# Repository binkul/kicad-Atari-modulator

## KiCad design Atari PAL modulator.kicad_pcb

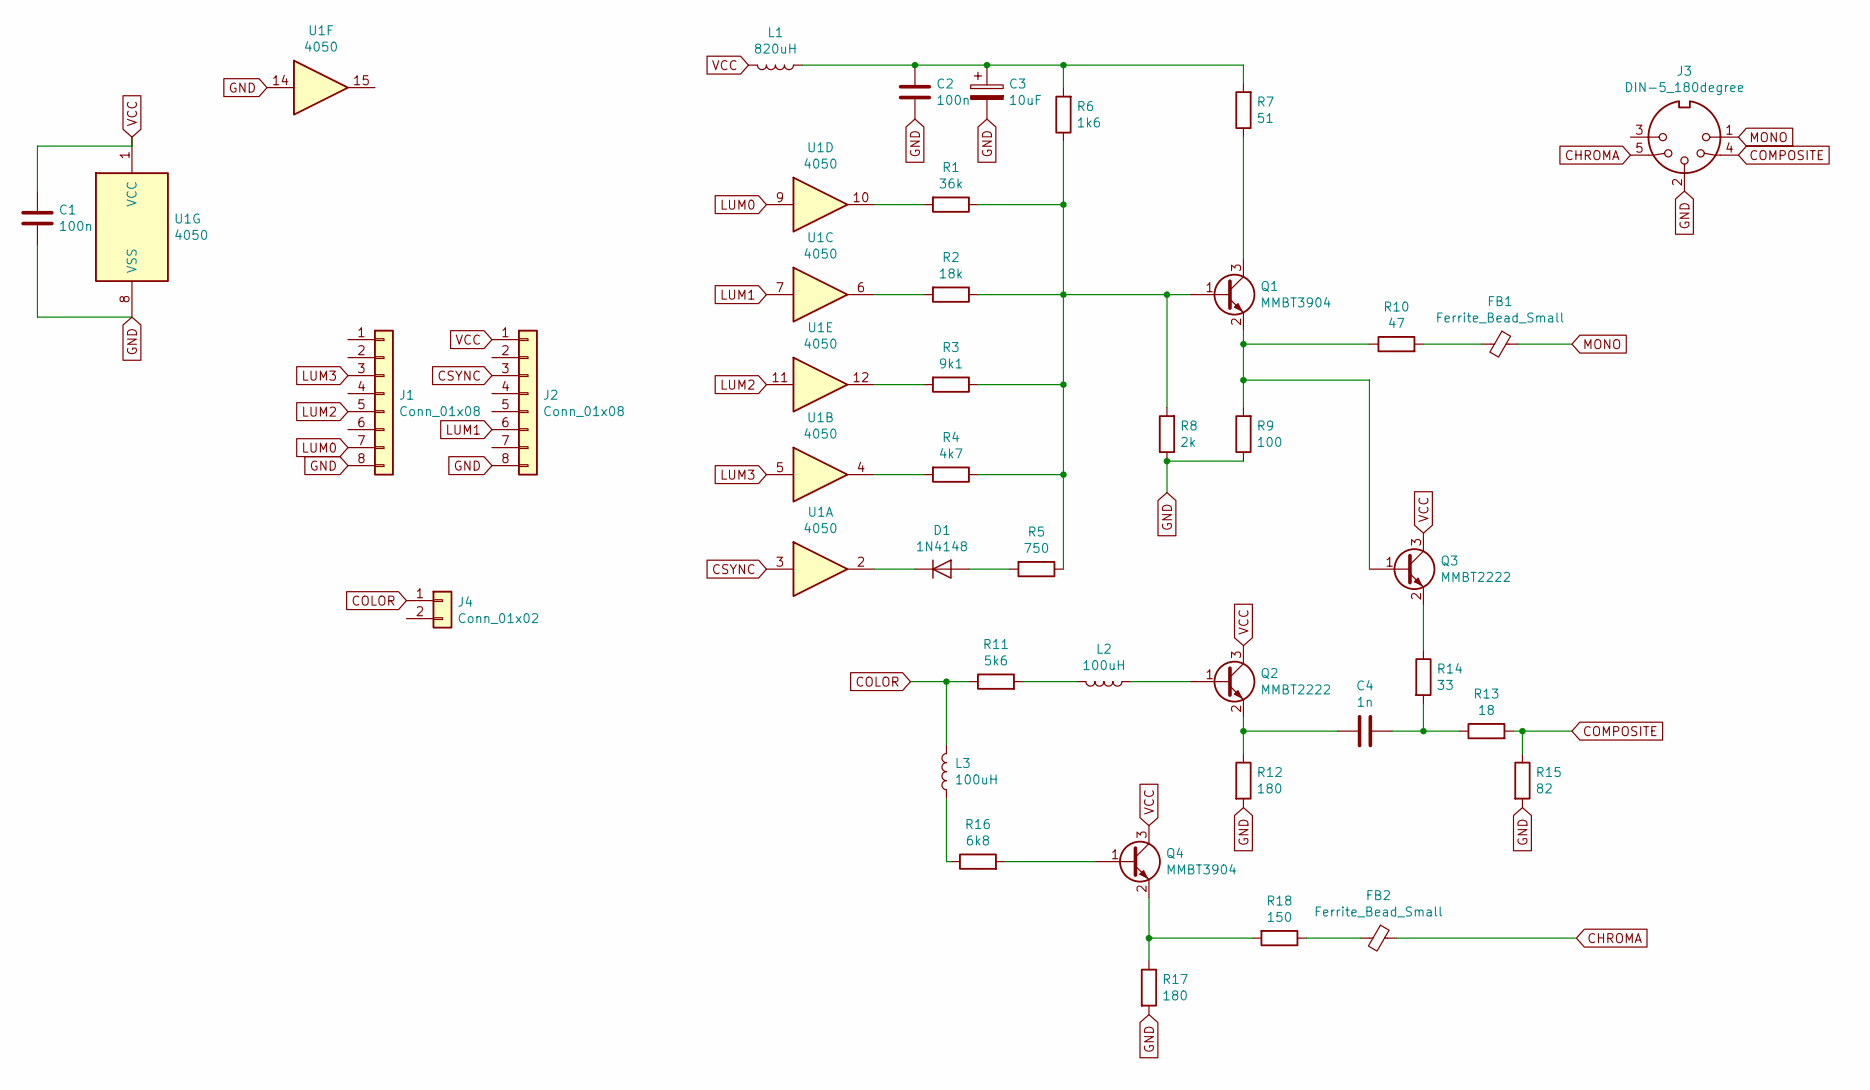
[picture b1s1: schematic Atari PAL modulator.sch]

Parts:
C1, C2: 100n; C_1206_3216Metric_Pad1.42x1.75mm_HandSolder
C3: 10uF; CP_Elec_5x5.7
C4: 1n; C_1206_3216Metric_Pad1.42x1.75mm_HandSolder
D1: 1N4148; D_MiniMELF_Handsoldering
FB1, FB2: Ferrite_Bead_Small; L_2816_7142Metric_Pad3.20x4.45mm_HandSolder
J1, J2: Conn_01x08; PinHeader_1x08_P2.54mm_Vertical
J3: DIN-5_180degree; DIN_5_pin
J4: Conn_01x02; PinHeader_1x02_P2.54mm_Horizontal
L1: 820uH; R_1812_4532Metric_Pad1.30x3.40mm_HandSolder
L2, L3: 100uH; L_1812_4532Metric_Pad1.30x3.40mm_HandSolder
Q1, Q4: MMBT3904; SOT-23
Q2, Q3: MMBT2222; SOT-23
R1: 36k; R_1206_3216Metric_Pad1.42x1.75mm_HandSolder
R2: 18k; R_1206_3216Metric_Pad1.42x1.75mm_HandSolder
R3: 9k1; R_1206_3216Metric_Pad1.42x1.75mm_HandSolder
R4: 4k7; R_1206_3216Metric_Pad1.42x1.75mm_HandSolder
R5: 750; R_1206_3216Metric_Pad1.42x1.75mm_HandSolder
R6: 1k6; R_1206_3216Metric_Pad1.42x1.75mm_HandSolder
R7: 51; R_1206_3216Metric_Pad1.42x1.75mm_HandSolder
R8: 2k; R_1206_3216Metric_Pad1.42x1.75mm_HandSolder
R9: 100; R_1206_3216Metric_Pad1.42x1.75mm_HandSolder
R10: 47; R_1206_3216Metric_Pad1.42x1.75mm_HandSolder
R11: 5k6; R_1206_3216Metric_Pad1.42x1.75mm_HandSolder
R12, R17: 180; R_1206_3216Metric_Pad1.42x1.75mm_HandSolder
R13: 18; R_1206_3216Metric_Pad1.42x1.75mm_HandSolder
R14: 33; R_1206_3216Metric_Pad1.42x1.75mm_HandSolder
R15: 82; R_1206_3216Metric_Pad1.42x1.75mm_HandSolder
R16: 6k8; R_1206_3216Metric_Pad1.42x1.75mm_HandSolder
R18: 150; R_1206_3216Metric_Pad1.42x1.75mm_HandSolder
U1: 4050; SOIC-16_3.9x9.9mm_P1.27mm

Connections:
CHROMA: FB2.1, J3.5
COLOR: J4.1, L3.2, R11.1
COMPOSITE: J3.4, R13.2, R15.1
CSYNC: J2.3, U1.3
GND: C1.2, C2.2, C3.2, J1.8, J2.8, J3.2, R8.1, R9.1, R12.2, R15.2, R17.2, U1.8 (VSS), U1.14
LUM0: J1.7, U1.9
LUM1: J2.6, U1.7
LUM2: J1.5, U1.11
LUM3: J1.3, U1.5
MONO: FB1.1, J3.1
unnamed: C2.1, C3.1, L1.1, R6.2, R7.2
unnamed: C4.1, R13.1, R14.2
unnamed: C4.2, Q2.2 (E), R12.1
unnamed: D1.1 (K), U1.2
unnamed: D1.2 (A), R5.2
unnamed: FB1.2, R10.2
unnamed: FB2.2, R18.1
unnamed: L2.1, Q2.1 (B)
unnamed: L2.2, R11.2
unnamed: L3.1, R16.1
unnamed: Q1.1 (B), R1.1, R2.1, R3.1, R4.1, R5.1, R6.1, R8.2
unnamed: Q1.2 (E), Q3.1 (B), R9.2, R10.1
unnamed: Q1.3 (C), R7.1
unnamed: Q3.2 (E), R14.1
unnamed: Q4.1 (B), R16.2
unnamed: Q4.2 (E), R17.1, R18.2
unnamed: R1.2, U1.10
unnamed: R2.2, U1.6
unnamed: R3.2, U1.12
unnamed: R4.2, U1.4
VCC: C1.1, J2.1, L1.2, Q2.3 (C), Q3.3 (C), Q4.3 (C), U1.1 (VCC)

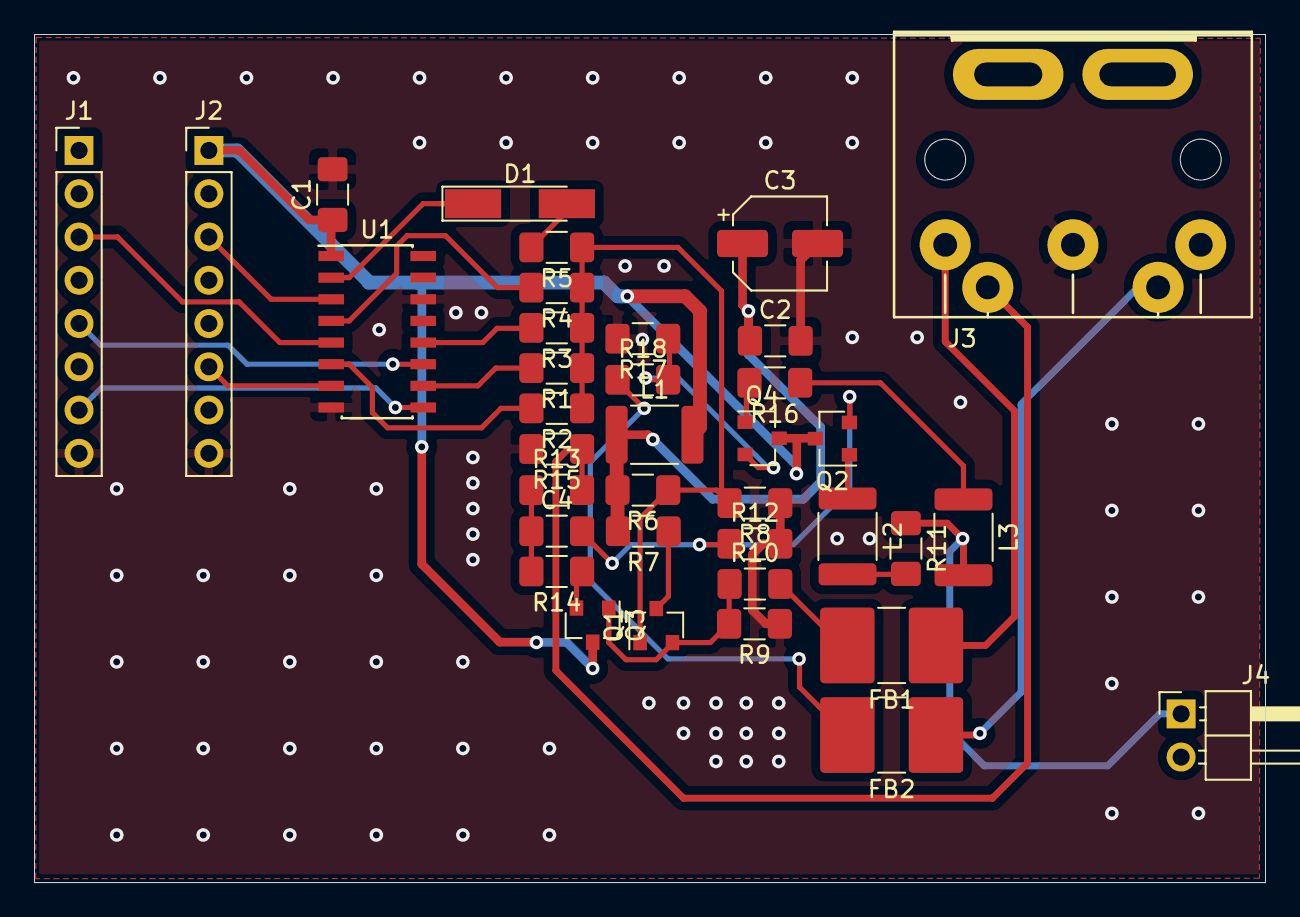
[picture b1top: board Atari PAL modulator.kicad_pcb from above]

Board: 2 copper layers, 72.3 x 49.8 mm, 37 parts (0 on the bottom side), 31 nets.

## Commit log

2020-08-25 All connections
